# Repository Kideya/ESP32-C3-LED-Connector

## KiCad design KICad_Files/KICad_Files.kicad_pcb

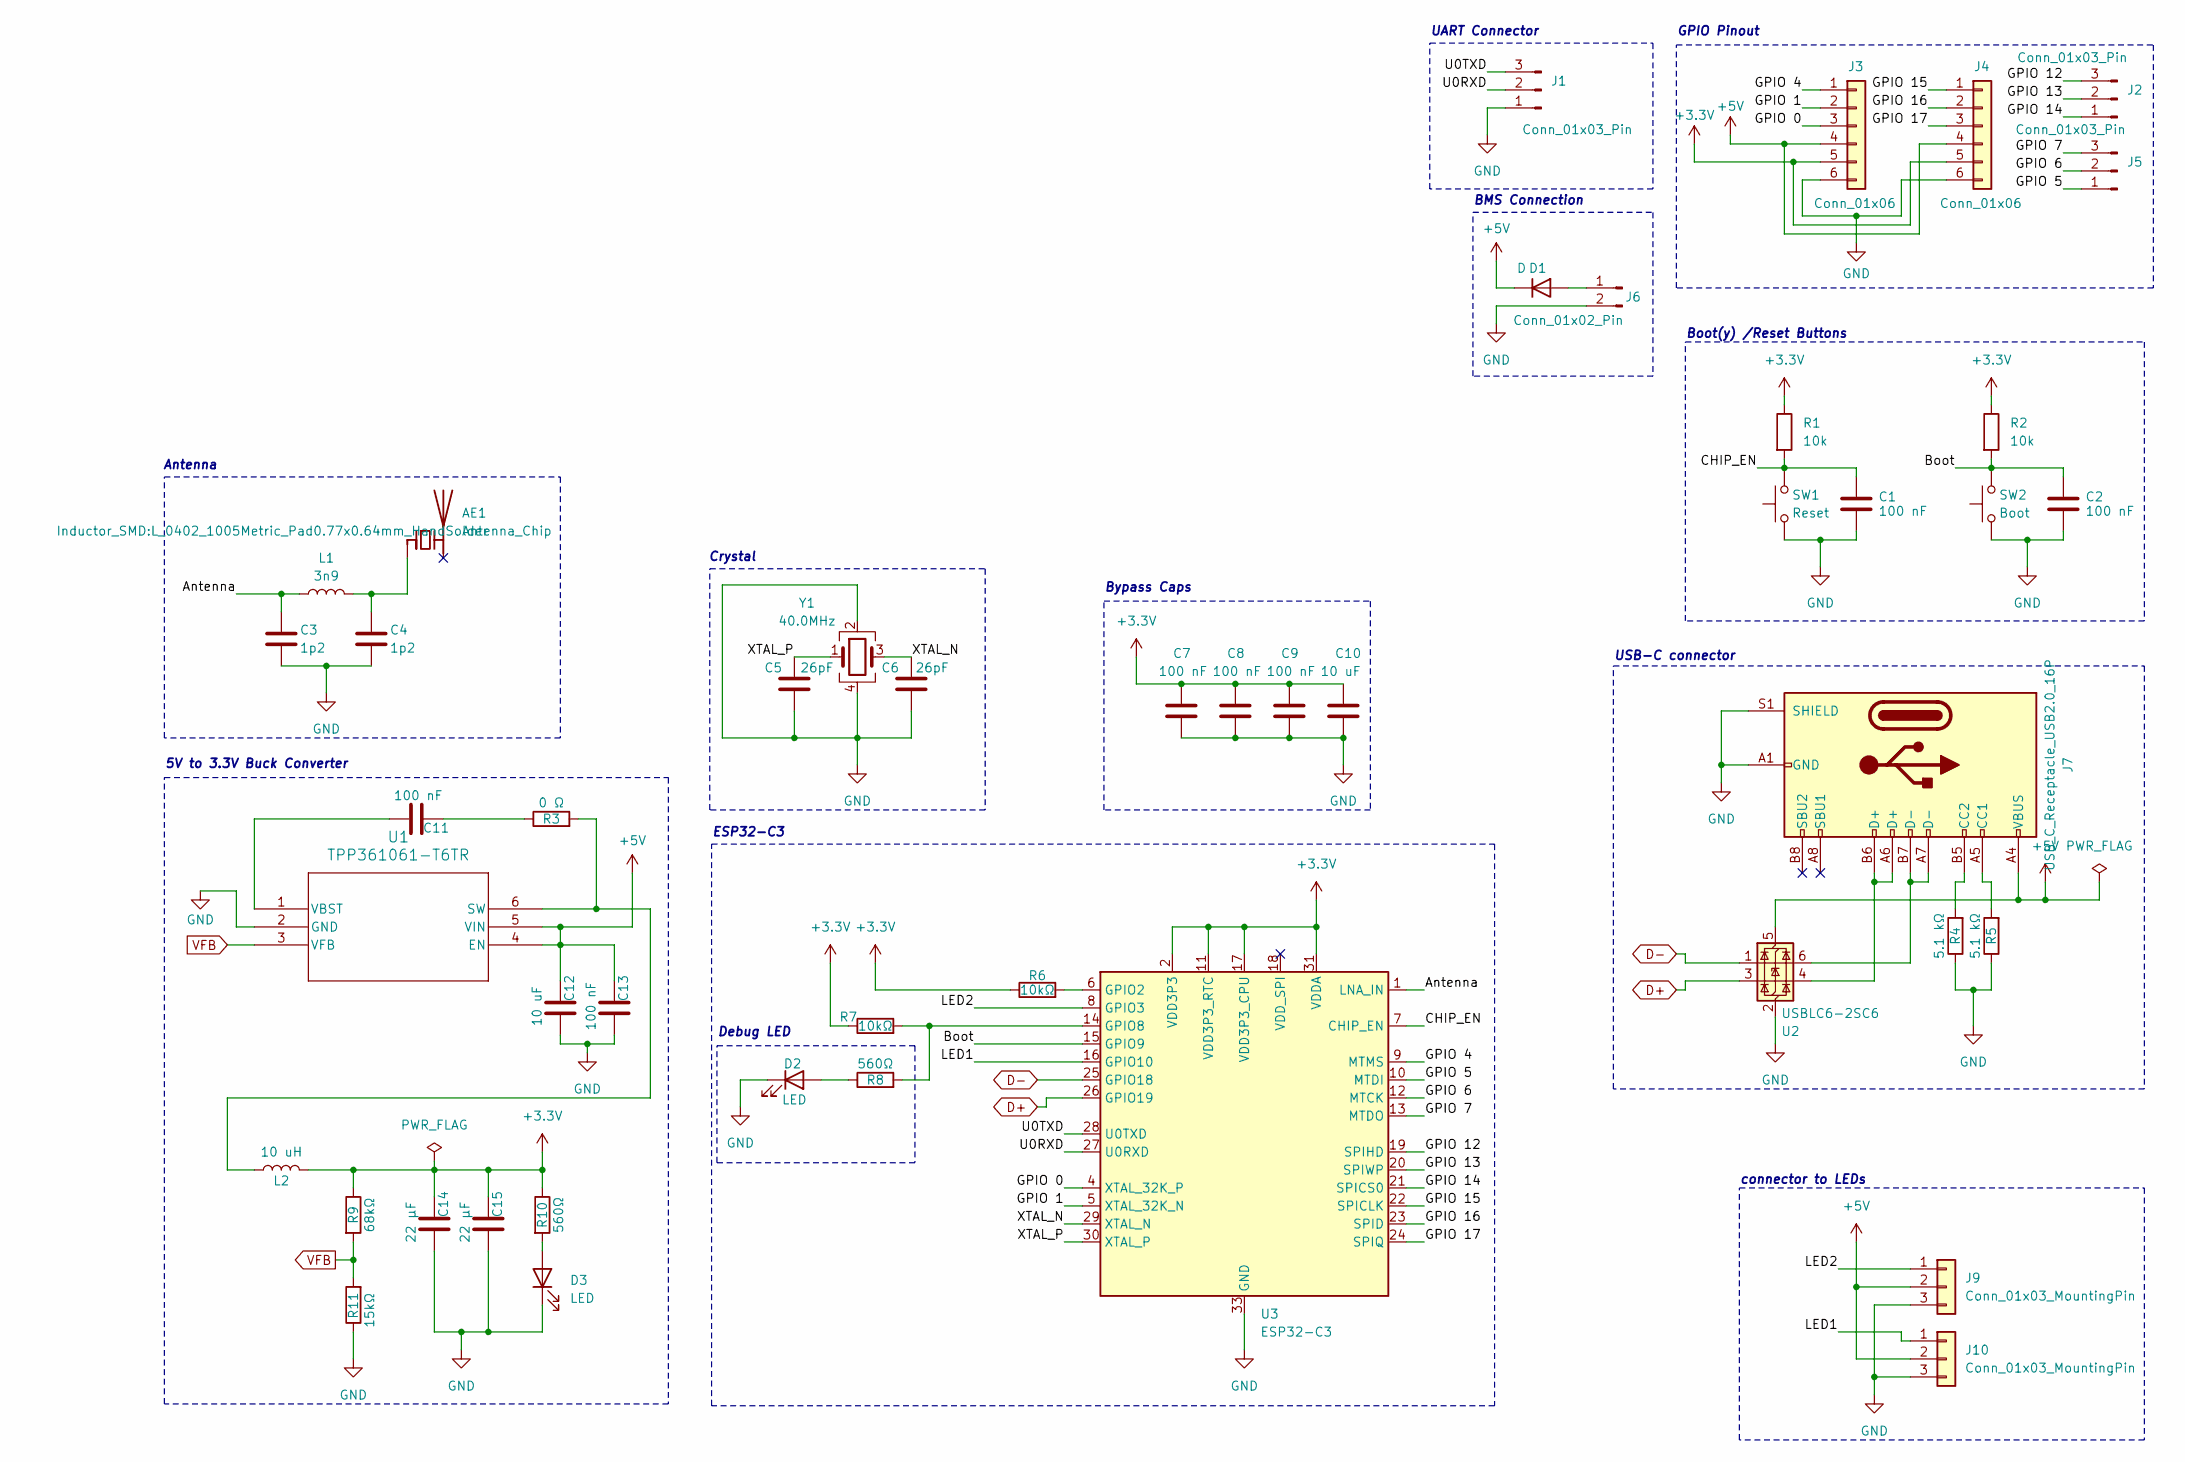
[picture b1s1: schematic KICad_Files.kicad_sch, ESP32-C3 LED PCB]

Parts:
AE1: Antenna_Chip; Johanson_2450AT43F0100
C1, C2, C7, C8, C9, C11, C13: 100 nF; C_0603_1608Metric_Pad1.08x0.95mm_HandSolder
C3, C4: 1p2; C_0402_1005Metric_Pad0.74x0.62mm_HandSolder
C5, C6: 26pF; C_0603_1608Metric_Pad1.08x0.95mm_HandSolder
C10, C12: 10 uF; C_0603_1608Metric_Pad1.08x0.95mm_HandSolder
C14, C15: 22 μF; C_0603_1608Metric_Pad1.08x0.95mm_HandSolder
D1: D; D_0603_1608Metric_Pad1.05x0.95mm_HandSolder
D2, D3: LED; LED_0805_2012Metric_Pad1.15x1.40mm_HandSolder
J1: Conn_01x03_Pin; PinHeader_1x03_P1.00mm_Vertical
J2, J5: Conn_01x03_Pin; PinHeader_1x03_P2.00mm_Vertical
J3, J4: Conn_01x06; PinHeader_1x06_P2.00mm_Vertical
J6: Conn_01x02_Pin; PinHeader_1x02_P2.00mm_Vertical
J7: USB_C_Receptacle_USB2.0_16P; USB_C_Receptacle_Palconn_UTC16-G
J9, J10: Conn_01x03_MountingPin; Molex_PicoBlade_53047-0310_1x03_P1.25mm_Vertical
L1: 3n9; L_0402_1005Metric_Pad0.77x0.64mm_HandSolder
L2: 10 uH; L_1008_2520Metric_Pad1.43x2.20mm_HandSolder
R1, R2: 10k; R_0603_1608Metric_Pad0.98x0.95mm_HandSolder
R3: 0 Ω; R_0603_1608Metric_Pad0.98x0.95mm_HandSolder
R4, R5: 5.1 kΩ; R_0603_1608Metric_Pad0.98x0.95mm_HandSolder
R6, R7: 10kΩ; R_0603_1608Metric_Pad0.98x0.95mm_HandSolder
R8, R10: 560Ω; R_0603_1608Metric_Pad0.98x0.95mm_HandSolder
R9: 68kΩ; R_0603_1608Metric_Pad0.98x0.95mm_HandSolder
R11: 15kΩ; R_0603_1608Metric_Pad0.98x0.95mm_HandSolder
SW1: Reset; RKB2SJK250SMTR LFS
SW2: Boot; RKB2SJK250SMTR LFS
U1: TPP361061-T6TR; SOT-23-6
U2: USBLC6-2SC6; SOT-23-6
U3: ESP32-C3; QFN-32-1EP_5x5mm_P0.5mm_EP3.7x3.7mm
Y1: 40.0MHz; Crystal_SMD_1210-4Pin_1.2x1.0mm

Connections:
+3.3V: C7.1, C8.1, C9.1, C10.1, C14.2, C15.2, J3.5, J4.5, L2.1, R1.1, R2.1, R6.1, R7.1, R9.1, R10.1, U3.2 (VDD3P3), U3.3 (VDD3P3), U3.11 (VDD3P3_RTC), U3.17 (VDD3P3_CPU), U3.31 (VDDA), U3.32 (VDDA)
+5V: C12.2, C13.2, D1.1 (K), J3.4, J4.4, J7.A4 (VBUS), J7.A9 (VBUS), J7.B4 (VBUS), J7.B9 (VBUS), J9.2, J10.2, U1.4 (EN), U1.5 (VIN), U2.5 (VBUS)
/Antenna: C3.1, L1.1, U3.1 (LNA_IN)
/Boot: C2.1, R2.2, SW2.2, U3.15 (GPIO9)
/CHIP_EN: C1.1, R1.2, SW1.2, U3.7 (CHIP_EN)
/GPIO 0: J3.3, U3.4 (XTAL_32K_P)
/GPIO 1: J3.2, U3.5 (XTAL_32K_N)
/GPIO 4: J3.1, U3.9 (MTMS)
/GPIO 5: J5.1, U3.10 (MTDI)
/GPIO 6: J5.2, U3.12 (MTCK)
/GPIO 7: J5.3, U3.13 (MTDO)
/GPIO 12: J2.3, U3.19 (SPIHD)
/GPIO 13: J2.2, U3.20 (SPIWP)
/GPIO 14: J2.1, U3.21 (SPICS0)
/GPIO 15: J4.1, U3.22 (SPICLK)
/GPIO 16: J4.2, U3.23 (SPID)
/GPIO 17: J4.3, U3.24 (SPIQ)
/LED1: J10.1, U3.16 (GPIO10)
/LED2: J9.1, U3.8 (GPIO3)
/U0RXD: J1.2, U3.27 (U0RXD)
/U0TXD: J1.3, U3.28 (U0TXD)
/XTAL_N: C6.1, U3.29 (XTAL_N), Y1.3
/XTAL_P: C5.1, U3.30 (XTAL_P), Y1.1
D+: U2.3 (I/O2), U3.26 (GPIO19)
D-: U2.1 (I/O1), U3.25 (GPIO18)
GND: C1.2, C2.2, C3.2, C4.2, C5.2, C6.2, C7.2, C8.2, C9.2, C10.2, C12.1, C13.1, C14.1, C15.1, D2.1 (K), D3.1 (K), J1.1, J3.6, J4.6, J6.2, J7.A1 (GND), J7.A12 (GND), J7.B1 (GND), J7.B12 (GND), J7.S1 (SHIELD), J9.3, J10.3, R4.1, R5.1, R11.1, SW1.1, SW2.1, U1.2 (GND), U2.2 (GND), U3.33 (GND), Y1.2, Y1.4
unnamed: AE1.1 (FEED), C4.1, L1.2
unnamed: C11.2, R3.1
unnamed: D1.2 (A), J6.1
unnamed: D2.2 (A), R8.1
unnamed: D3.2 (A), R10.2
unnamed: J7.A5 (CC1), R5.2
unnamed: J7.B5 (CC2), R4.2
unnamed: J7.A6 (D+), J7.B6 (D+), U2.4 (I/O2)
unnamed: J7.A7 (D-), J7.B7 (D-), U2.6 (I/O1)
unnamed: L2.2, R3.2, U1.6 (SW)
unnamed: C11.1, U1.1 (VBST)
unnamed: R6.2, U3.6 (GPIO2)
unnamed: R7.2, R8.2, U3.14 (GPIO8)
VFB: R9.2, R11.2, U1.3 (VFB)

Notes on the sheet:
UART Connector
Antenna
GPIO Pinout
Bypass Caps
Boot(y) /Reset Buttons
Crystal
5V to 3.3V Buck Converter
USB-C connector
connector to LEDs
Debug LED
ESP32-C3
BMS Connection

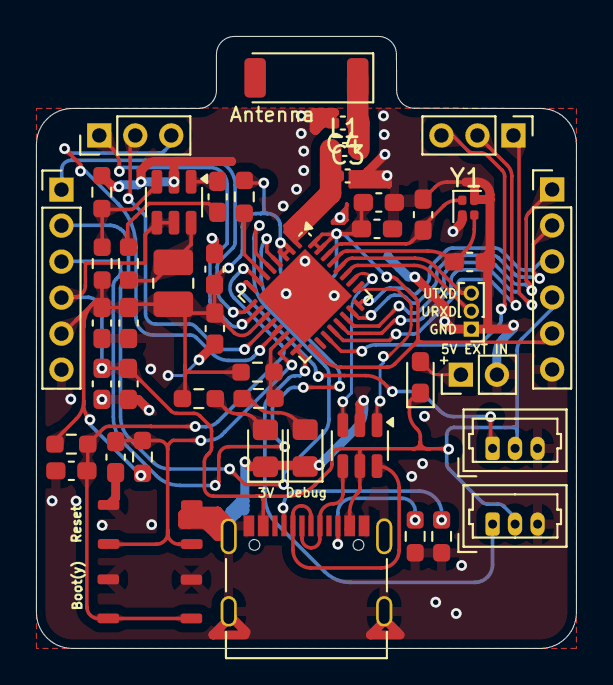
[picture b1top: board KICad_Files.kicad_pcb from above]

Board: 2 copper layers, 30.0 x 34.0 mm, 47 parts (0 on the bottom side), 40 nets.

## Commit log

2025-03-05 Changed from 3 to 2 connector because of ESP32-C3 Limitations
2025-04-26 Switched the pi-filter components to 0402 size and changed the values
2025-04-26 Switched crystal size and changed GPIO02 to be pulled high instead of low
2025-04-26 fixed ground plane issues with the antenna
